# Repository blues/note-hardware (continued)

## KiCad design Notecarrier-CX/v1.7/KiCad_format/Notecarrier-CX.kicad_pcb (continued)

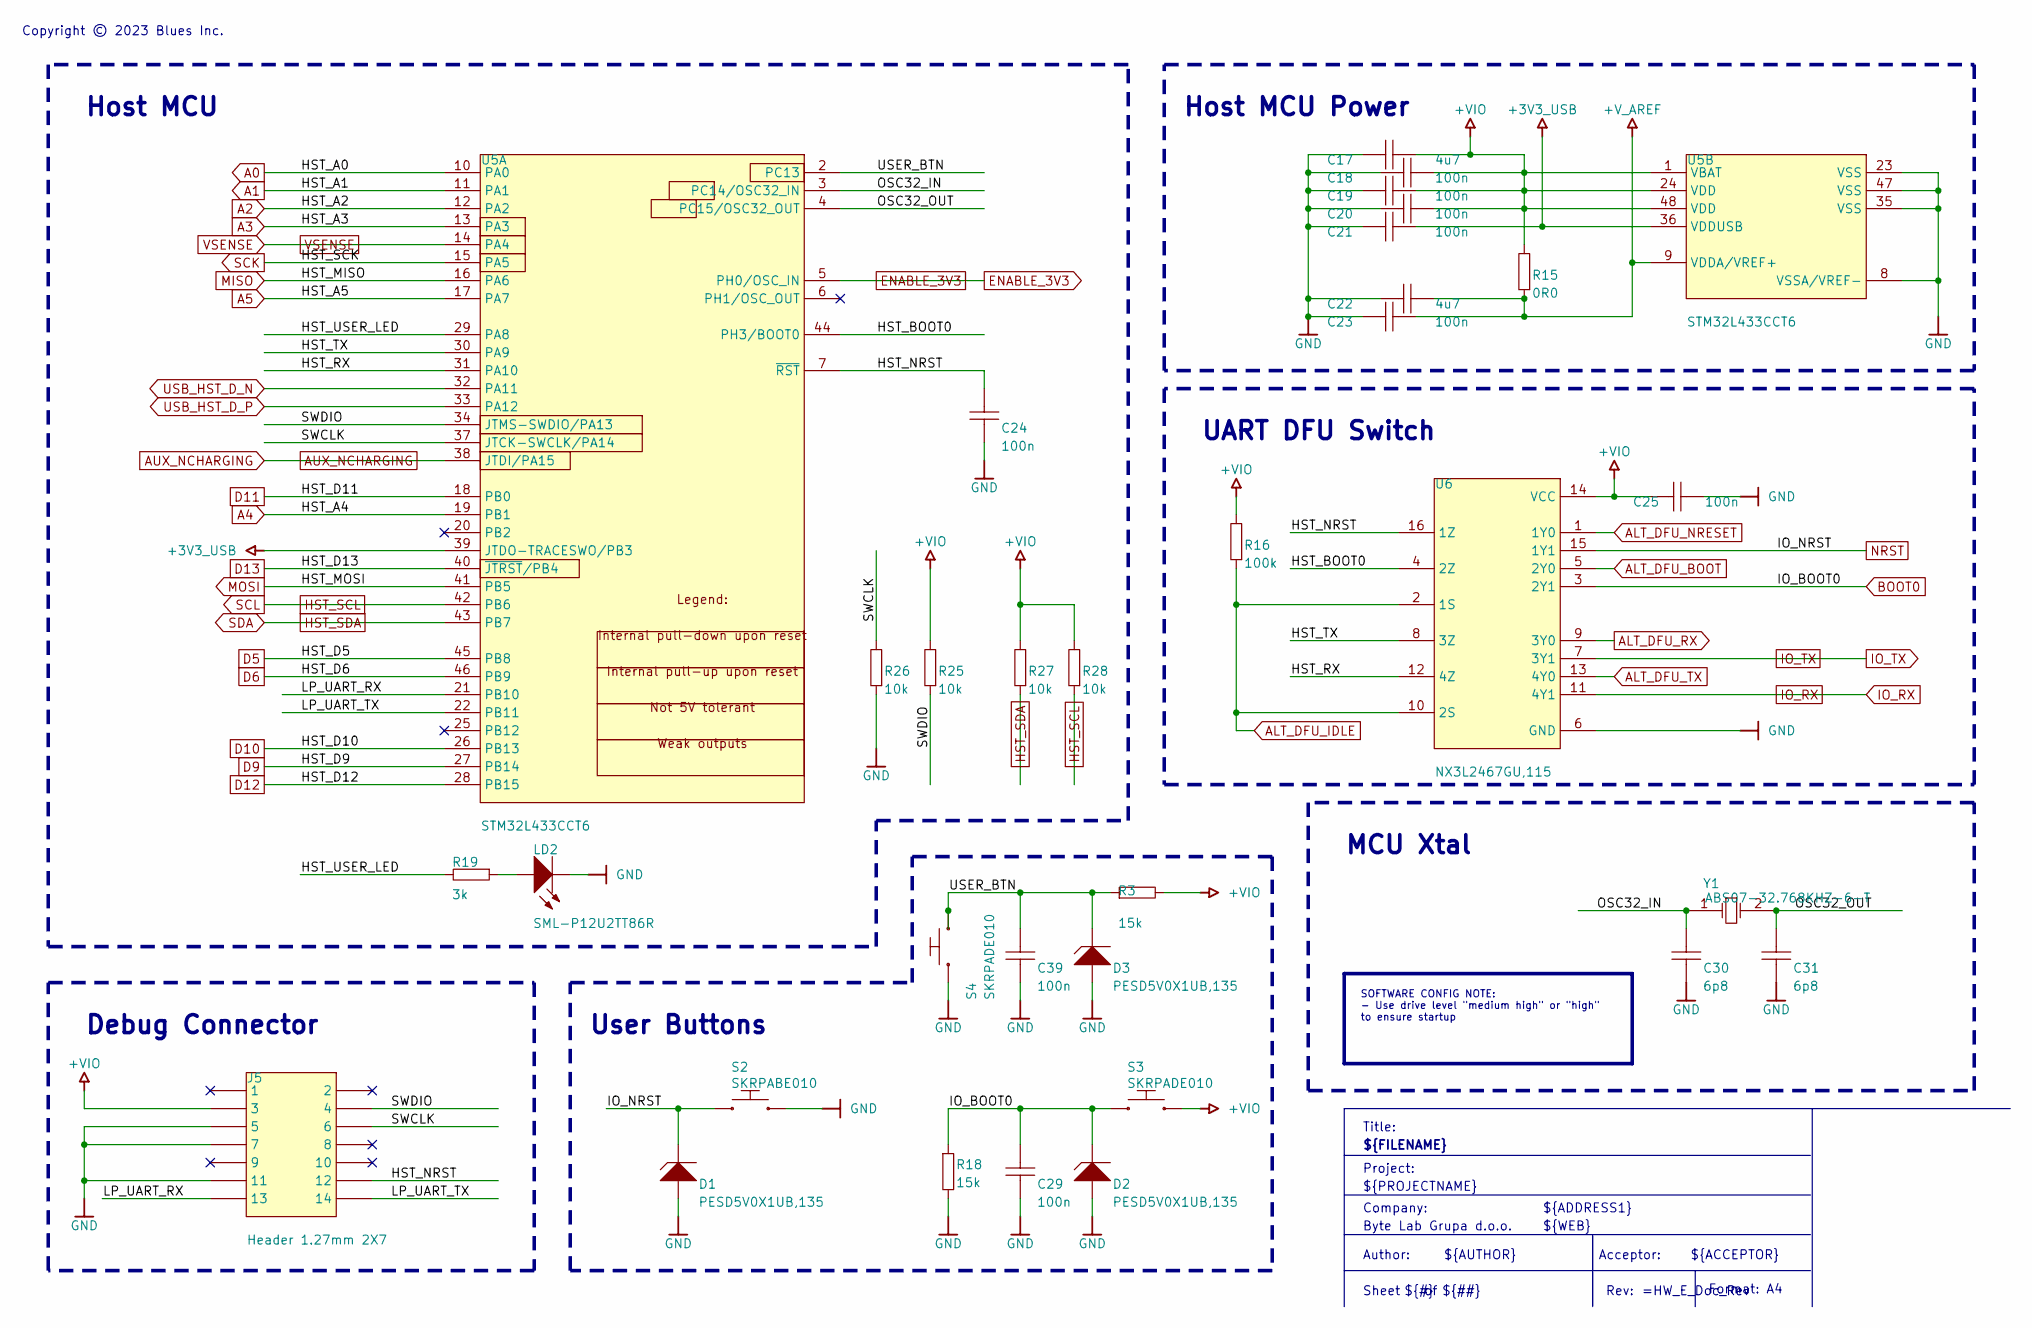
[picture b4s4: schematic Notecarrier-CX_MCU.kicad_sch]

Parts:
C17, C22: 4u7; C-0603; MANUFACTURER PART NUMBER N/A
C18, C19, C20, C21, C23, C24, C25, C29, C39: 100n; C-0402; MANUFACTURER PART NUMBER N/A
C30, C31: 6p8; C-0402; MANUFACTURER PART NUMBER CL05C6R8CB5NNNC
D1, D2, D3: PESD5V0X1UB,135; SOD-523F; MANUFACTURER PART NUMBER PESD5V0X1UB,135
J5: Header 1.27mm 2X7; Header 1.27mm 2X7 SMD; MANUFACTURER PART NUMBER FTSH-107-01-L-DV-K
LD2: SML-P12U2TT86R; LED-0402; MANUFACTURER PART NUMBER SML-P12U2TT86R
R3, R18: 15k; R-0402; MANUFACTURER PART NUMBER N/A
R15: 0R0; R-0603; MANUFACTURER PART NUMBER N/A
R16: 100k; R-0402; MANUFACTURER PART NUMBER N/A
R19: 3k; R-0402; MANUFACTURER PART NUMBER N/A
R25, R26, R27, R28: 10k; R-0402; MANUFACTURER PART NUMBER N/A
S2: SKRPABE010; Tact Switch SKRPADE010; MANUFACTURER PART NUMBER SKRPABE010
S3, S4: SKRPADE010; Tact Switch SKRPADE010; MANUFACTURER PART NUMBER SKRPADE010
U5: STM32L433CCT6; QFP50P900X900X160-48; MANUFACTURER PART NUMBER STM32L433CCT6
U6: NX3L2467GU,115; QFN40P180X260X55-16N; MANUFACTURER PART NUMBER NX3L2467GU,115
Y1: ABS07-32.768KHZ-6-T; XTAL_3.2x1.5 MM; MANUFACTURER PART NUMBER ABS07-32.768KHZ-6-T

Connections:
+3V3_USB: C21.2, U5.36 (VDDUSB), U5.39 (JTDO-TRACESWO/PB3); also elsewhere on the board
+VIO: C17.2, C18.2, C19.2, C20.2, C25.1, J5.3, R3.2, R15.2, R16.2, R25.2, R27.2, R28.2, S3.2, U5.1 (VBAT), U5.24 (VDD), U5.48 (VDD), U6.14 (VCC); also elsewhere on the board
+V_AREF: C22.2, C23.2, R15.1, U5.9 (VDDA/VREF+); also elsewhere on the board
/MCU/HST_BOOT0: U5.44 (PH3/BOOT0), U6.4 (2Z)
/MCU/HST_NRST: C24.2, J5.12, U5.7 (~RST), U6.16 (1Z)
/MCU/HST_RX: U5.31 (PA10), U6.12 (4Z)
/MCU/HST_TX: U5.30 (PA9), U6.8 (3Z)
/MCU/HST_USER_LED: R19.2, U5.29 (PA8)
/MCU/LP_UART_RX: J5.13, U5.21 (PB10)
/MCU/LP_UART_TX: J5.14, U5.22 (PB11)
/MCU/OSC32_IN: C30.2, U5.3 (PC14/OSC32_IN), Y1.1 (OSC1)
/MCU/OSC32_OUT: C31.2, U5.4 (PC15/OSC32_OUT), Y1.2 (OSC2)
/MCU/SWCLK: J5.6, R26.2, U5.37 (JTCK-SWCLK/PA14)
/MCU/SWDIO: J5.4, R25.1, U5.34 (JTMS-SWDIO/PA13)
/MCU/USER_BTN: C39.2, D3.2 (K), R3.1, S4.2, U5.2 (PC13)
A0: U5.10 (PA0); also elsewhere on the board
A1: U5.11 (PA1); also elsewhere on the board
A2: U5.12 (PA2); also elsewhere on the board
A3: U5.13 (PA3); also elsewhere on the board
A4: U5.19 (PB1); also elsewhere on the board
A5: U5.17 (PA7); also elsewhere on the board
ALT_DFU_BOOT: U6.5 (2Y0); also elsewhere on the board
ALT_DFU_IDLE: R16.1, U6.2 (1S), U6.10 (2S); also elsewhere on the board
ALT_DFU_NRESET: U6.1 (1Y0); also elsewhere on the board
ALT_DFU_RX: U6.9 (3Y0); also elsewhere on the board
ALT_DFU_TX: U6.13 (4Y0); also elsewhere on the board
AUX_NCHARGING: U5.38 (JTDI/PA15); also elsewhere on the board
BOOT0: C29.2, D2.2 (K), R18.1, S3.1, U6.3 (2Y1); also elsewhere on the board
D5: U5.45 (PB8); also elsewhere on the board
D6: U5.46 (PB9); also elsewhere on the board
D9: U5.27 (PB14); also elsewhere on the board
D10: U5.26 (PB13); also elsewhere on the board
D11: U5.18 (PB0); also elsewhere on the board
D12: U5.28 (PB15); also elsewhere on the board
D13: U5.40 (~JTRST/PB4); also elsewhere on the board
ENABLE_3V3: U5.5 (PH0/OSC_IN); also elsewhere on the board
GND: C17.1, C18.1, C19.1, C20.1, C21.1, C22.1, C23.1, C24.1, C25.2, C29.1, C30.1, C31.1, C39.1, D1.1 (A), D2.1 (A), D3.1 (A), J5.5, J5.7, J5.11, LD2.2 (K), R18.2, R26.1, S2.2, S4.1, U5.8 (VSSA/VREF-), U5.23 (VSS), U5.35 (VSS), U5.47 (VSS), U6.6 (GND); also elsewhere on the board
HST_SCL: R28.1, U5.42 (PB6); also elsewhere on the board
HST_SDA: R27.1, U5.43 (PB7); also elsewhere on the board
IO_RX: U6.11 (4Y1); also elsewhere on the board
IO_TX: U6.7 (3Y1); also elsewhere on the board
MISO: U5.16 (PA6); also elsewhere on the board
MOSI: U5.41 (PB5); also elsewhere on the board
NRST: D1.2 (K), S2.1, U6.15 (1Y1); also elsewhere on the board
unnamed: LD2.1 (A), R19.1
SCK: U5.15 (PA5); also elsewhere on the board
USB_HST_D_N: U5.32 (PA11); also elsewhere on the board
USB_HST_D_P: U5.33 (PA12); also elsewhere on the board
VSENSE: U5.14 (PA4); also elsewhere on the board

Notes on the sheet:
${COMPANY}
${#}
Debug Connector
UART DFU Switch
Host MCU Power
Copyright © 2023 Blues Inc.
Company:
${WEB}
${REVISION}
Author:
Format: A4
User Buttons
Project:
MCU Xtal
Rev:
${FILENAME}
${ADDRESS1}
Host MCU
${ACCEPTOR}
${##}
${AUTHOR}
Sheet
Acceptor:
Title:
${PROJECTNAME}
SOFTWARE CONFIG NOTE: - Use drive level "medium high" or "high" to ensure startup

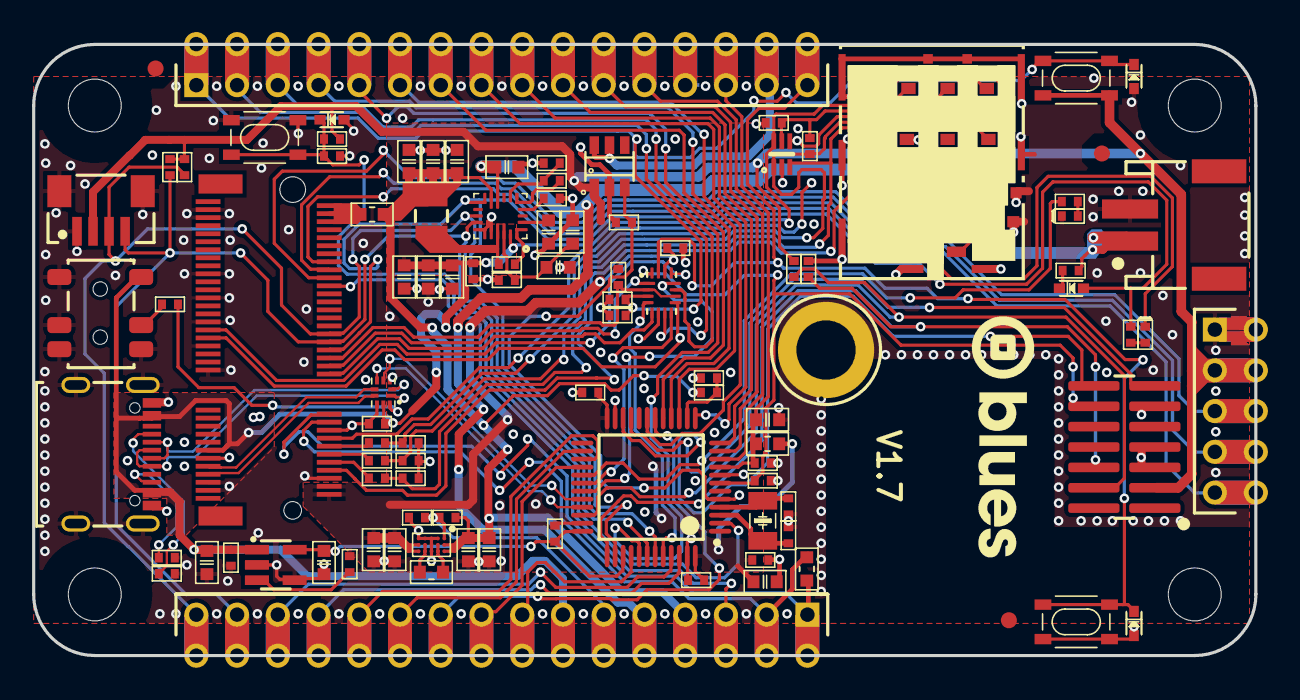
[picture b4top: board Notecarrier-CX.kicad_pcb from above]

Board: 4 copper layers, 76.2 x 38.1 mm, 101 parts (0 on the bottom side), 89 nets.

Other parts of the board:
FD1, FD2, FD5: Fiducial mark; Fiducial mark 1mm

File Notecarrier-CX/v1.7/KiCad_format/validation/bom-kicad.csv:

"Reference","Value","MPN","DNP"
"ASS1","KNOB M2.5x4-INOX","6000-168",""
"C1","10u","2006-831",""
"C2","100n","2000-908",""
"C3","33p","2001-377",""
"C4","33p","2001-377",""
"C5","33p","2001-377",""
"C6","10u","2006-831",""
"C7","10u","2006-831",""
"C8","47n/50V","2003-965",""
"C9","100n","2000-908",""
"C10","100n","2000-908",""
"C11","10u","2006-831",""
"C12","10u","2006-831",""
"C13","4u7","2003-721",""
"C14","10u","2006-831",""
"C15","100n","2004-296",""
"C16","4u7","2003-721",""
"C17","4u7","2003-721",""
"C18","100n","2000-908",""
"C19","100n","2000-908",""
"C20","100n","2000-908",""
"C21","100n","2000-908",""
"C22","4u7","2003-721",""
"C23","100n","2000-908",""
"C24","100n","2000-908",""
"C25","100n","2000-908",""
"C26","4u7","2003-721",""
"C27","100n","2000-908",""
"C28","4u7","2003-721",""
"C29","100n","2000-908",""
"C30","6p8","2001-291",""
"C31","6p8","2001-291",""
"C32","100n","2000-908",""
"C33","10u","2006-831",""
"C34","10u","2006-831",""
"C35","10u","2006-831",""
"C36","10u","2006-831",""
"C37","10u","2006-831",""
"C38","10u","2006-831",""
"C39","100n","2000-908",""
"D1","PESD5V0X1UB,135","2004-110",""
"D2","PESD5V0X1UB,135","2004-110",""
"D3","PESD5V0X1UB,135","2004-110",""
"D4","1N4148WT-7","2001-986",""
"J1","BM04B-SRSS-TB(LF)(SN)","2007-322",""
"J3","MDT580E01002","2009-243",""
"J4","SF72S006VBDR2500","2007-458",""
"J5","Header 1.27mm 2X7","2009-203",""
"L1","MCKK1608T1R0MN","2003-989",""
"L2","3u3","2004-215",""
"LD1","SML-P12WTT86R","2007-660",""
"LD2","SML-P12U2TT86R","2006-852",""
"P3","12402012E212A","2008-437",""
"P5","S2B-PH-SM4-K-TB","2007-662",""
"R1","5k1","2004-098",""
"R2","5k1","2004-098",""
"R3","15k","2001-157",""
"R4","0R0","2000-723","DNP"
"R5","22R","2001-170",""
"R6","22R","2001-170",""
"R7","15k","2001-157",""
"R8","22R","2001-170",""
"R9","0R0","2000-723",""
"R10","10M","2002-832",""
"R11","3k","2001-570",""
"R12","3k","2001-570",""
"R13","11k","2004-237",""
"R14","15k","2001-157",""
"R15","0R0","2000-723",""
"R16","100k","2000-727",""
"R17","1M","2000-734",""
"R18","15k","2001-157",""
"R19","3k","2001-570",""
"R20","11k","2004-237",""
"R21","1M","2000-734",""
"R22","11k","2004-237",""
"R23","10M","2002-832",""
"R24","4M3","2007-009",""
"R25","10k","2000-729",""
"R26","10k","2000-729",""
"R27","10k","2000-729",""
"R28","10k","2000-729",""
"S1","SSSS820101","2009-940",""
"S2","SKRPABE010","2009-324",""
"S3","SKRPADE010","2007-145",""
"S4","SKRPADE010","2007-145",""
"STANDOFF1","9774040151R","6000-267",""
"TVS1","PESD5V0L5UV,125","2007-452",""
"U1","NX3DV42GU","2005-299",""
"U2","RT6160BWSC","2008-326",""
"U3","BQ25628ERYKR","2008-206",""
"U4","TPS22917DBVR","2008-396",""
"U5","STM32L433CCT6","2009-272",""
"U6","NX3L2467GU,115","2009-148",""
"U7","TLV77033PDBVR","2009-790",""
"Y1","ABS07-32.768KHZ-6-T","2005-489",""

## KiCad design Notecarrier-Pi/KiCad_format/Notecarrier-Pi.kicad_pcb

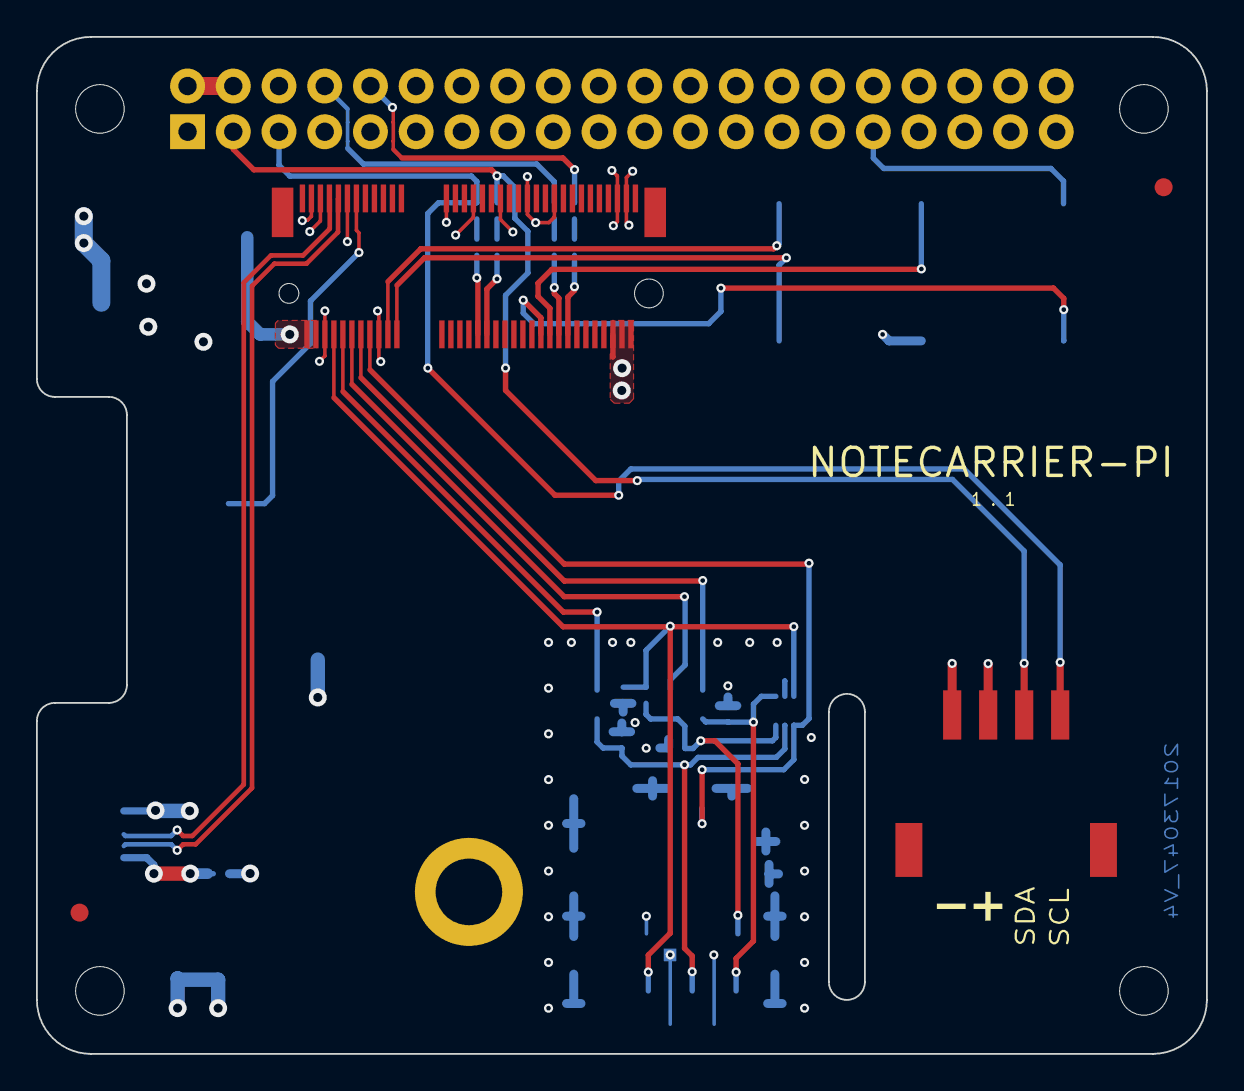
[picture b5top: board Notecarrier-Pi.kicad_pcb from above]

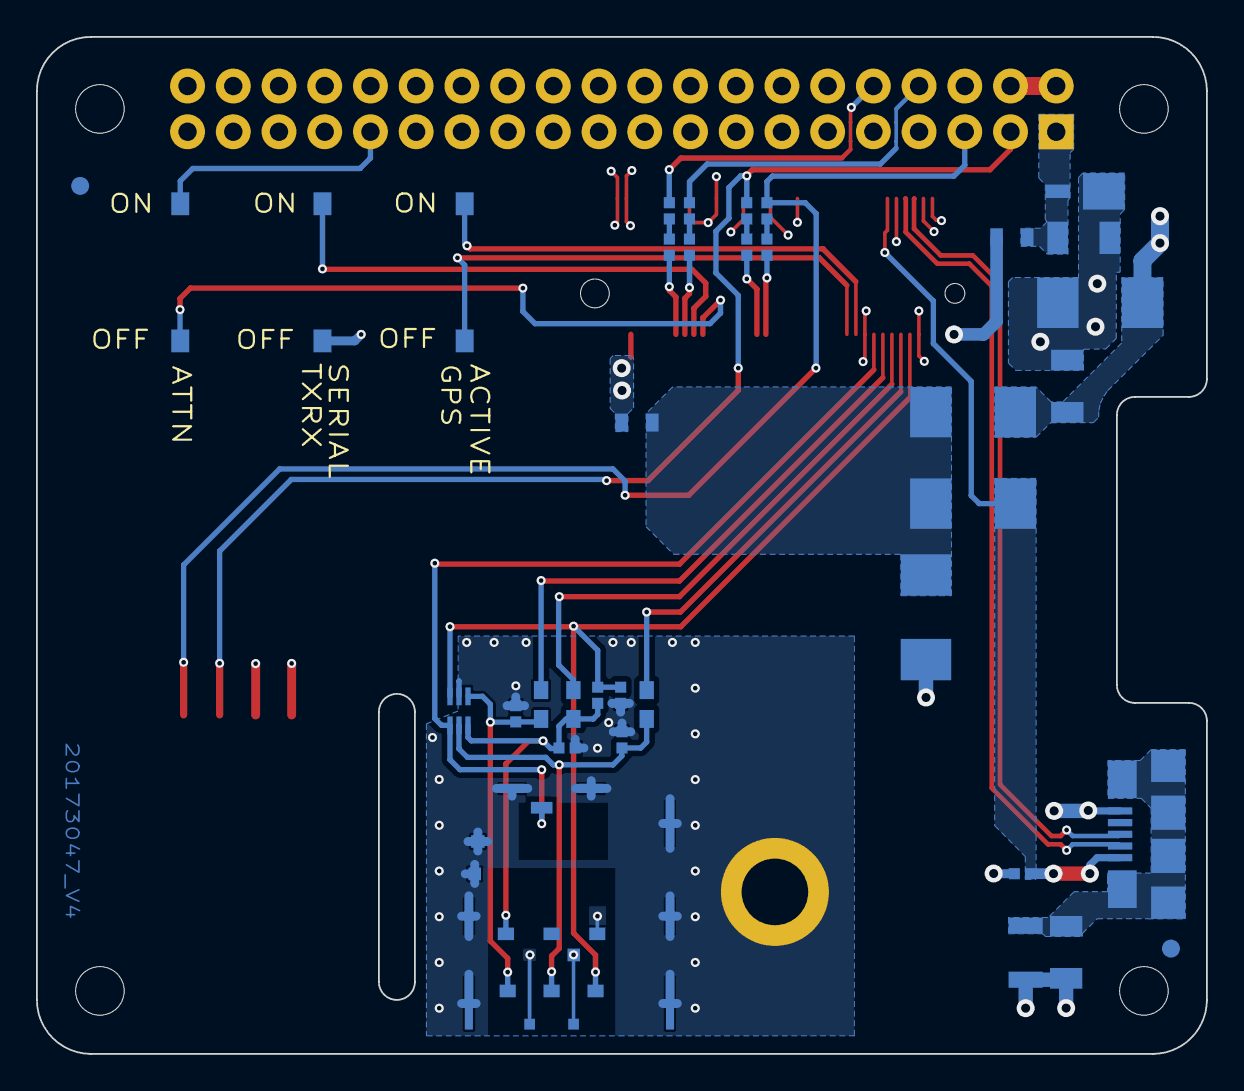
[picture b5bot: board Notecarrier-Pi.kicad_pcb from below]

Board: 4 copper layers, 65.0 x 56.5 mm, 46 parts (37 on the bottom side), 35 nets.

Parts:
C1, C2: 22u/25V-X5R; CS-C-1206
C3, C7: 100n/16V; CS-C-0402
C4, C5, C6: 33p/50V-C0G; CS-C-0402
C8: 10n/1kV; CS-C-1206
DS1, DS2: STPS3H100U; SMB
DSW1, DSW2, DSW3: DIP-SW-CHS-01TB; DSS-CHS-01TB
F1: SF-0603F150-2; FS-0603
F2: 3.5A/32V; FS-0603
FID1, FID2, FID3, FID4: TPS; FIDUCIAL
H1, H2, H3, H4: MountingHole; FORO-0270-U_smaller-clearance
J1: 2223; J-20x2-0254-FDT-SSQX03
J2: NanoSIM - SF72S006VBAR2500; J-NANOSIM-SF72S006VBA_NO-FILL
J3: MDT420E01001; J-75-0050-MOS-M2-E
J4: 10118192-0002LF; J-5-0065-FOS-USB10118192-NOF
J5: GROVE; J-4-0200-MOS-GROVE_NO-SILK
OBJ1: 9774025151R; DIST-WASMSIM0250
R1, R2, R3: 22R; RS-0603
R4: 15k; RS-0402
R5: 1M; RS-1206
R6, R7, R8, R9, R10, R11, R12, R13: 100R; RS-0402
TVS1, TVS3: SM6T6V8A; SMB
TVS2: SM2T3V3A; D-DO216AA_NO-SILK
TVS4: ESDLC5V0M5-TP; SOT666_NO-SILK

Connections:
/ATTN: DSW3.2, J1.31
/AUX_EN: DSW2.2, J3.56 (AUX_EN_P)
/AUX_RX: J1.8, R10.1
/AUX_RX_P: J3.58 (AUX_RX_P), R11.2
/AUX_TX: J1.10, R12.1
/AUX_TX_P: J3.60 (AUX_TX_P), R13.2
/SCL: J1.5, J5.1, R6.1
/SDA: J1.3, J5.2, R8.1
/SIM_CLK: J3.14 (SIM_CLK), R3.1
/SIM_IO: J3.12 (SIM_IO), R1.1
/SIM_NPRESENT: J2.DSW, J3.16 (SIM_NPRESENT), TVS4.4 (K3)
/SIM_RST: J3.10 (SIM_RST), R2.1
/SIM_VCC: C3.1, J2.C1 (VCC), J3.8 (SIM_VCC), R4.2, TVS4.3 (K2)
/USB_DM: J3.9 (USB_DM), J4.2 (D-)
/USB_DP: J3.7 (USB_DP), J4.3 (D+)
GND: C1.2, C2.2, C3.2, C4.2, C5.2, C6.2, C7.2, C8.2, J1.6, J1.9, J1.14, J1.20, J1.25, J1.30, J1.34, J1.39, J2.C5 (GND), J2.CSW, J2.SH, J3.3 (GND), J3.5 (GND), J3.6 (GND), J3.11 (GND), J3.18 (GND), J3.33 (GND), J3.39 (GND), J3.45 (GND), J3.51 (GND), J3.57 (GND), J3.71 (GND), J3.73 (GND), J4.5 (GND), J5.4, OBJ1.1, R5.2, TVS1.2 (A2), TVS2.2 (A2), TVS3.2 (A2), TVS4.2 (A)
unnamed: C5.1, J2.C3 (CLK), R3.2, TVS4.1 (K1)
unnamed: C6.1, J2.C7 (I/O), R1.2, R4.1, TVS4.6 (K5)
unnamed: C4.1, J2.C2 (RST), R2.2, TVS4.5 (K4)
unnamed: DSW3.1, J3.54 (ATTN_P)
unnamed: J3.40 (SCL_P), R7.2
unnamed: J3.42 (SDA_P), R9.2
unnamed: DSW1.1, J3.22 (VACT_GPS_IN)
unnamed: C8.1, J4.6 (Shield), R5.1
unnamed: R6.2, R7.1
unnamed: R8.2, R9.1
unnamed: R10.2, R11.1
unnamed: R12.2, R13.1
V+: C2.1, DS2.2 (A), J1.2, J1.4, TVS3.1 (A1)
VACT_GPS_OUT: DSW1.2, J3.20 (VACT_GPS_OUT)
VIO: C1.1, F1.1, J1.1, TVS2.1 (A1)
VIO_P: DSW2.1, F1.2, J3.2 (VIO_P), J3.4 (VIO_P), J5.3
VMODEM: DS1.1 (K), DS2.1 (K), F2.1, TVS1.1 (A1)
VMODEM_P: F2.2, J3.70 (VMODEM_P), J3.72 (VMODEM_P), J3.74 (VMODEM_P)
VUSB: C7.1, DS1.2 (A), J3.13 (VUSB), J4.1 (VBUS)

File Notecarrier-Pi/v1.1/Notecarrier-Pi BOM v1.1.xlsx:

PROJECT |  | 2017-3047 (NOTECARRIER-M2-PI) |  | Blues Inc
REVISION |  | 4
SCHEMATIC |  | 20173047_NOTECARRIER-M2-PI_V4
DATA |  | 23/09/2020
Item | Quantity | Reference | Part | MPN | Description | Temperature | Distributor | Type | Package | Database
1 | 1 | CS1 | CS V4 4L 18um |  | C.S. NOTECARRIER-M2-PI V4 (65X56.5)mm 4L/SO/SR ENIG TG150 sp=1.6mm Cu=18um | TG150 | WE
2 | 2 | C1,C2 | 22u/25V-X5R |  | CHIP CAP.CER. 22uF 25V 10% X5R 1206 | -55°..+85° | FAE | SMD | CS-C-1206 | 30650
3 | 2 | C3,C7 | 100n/16V |  | CHIP CAP.CER. 100nF 16V 10% X7R 0402 |  | FAE | SMD | CS-C-0402 | 22452
4 | 3 | C4,C5,C6 | 33p/50V-C0G |  | CHIP CAP.CER. 33pF 50V 5% C0G 0402 |  | FAE | SMD | CS-C-0402 | 38594
5 | 1 | C8 | 10n/1kV |  | CHIP CAP.CER. 10nF 1000V 10% X7R 1206 |  | FAE | SMD | CS-C-1206 | 28470
6 | 3 | DSW1,DSW2,DSW3 | DIP-SW-CHS-01TB |  | DIP SWITCH 1P/D NERO CHS-01TB COPAL SMT | -40°..+85° | FAE | SMD | DSS-CHS-01TB | 33083
7 | 2 | DS1,DS2 | STPS3H100U | STPS3H100U | DIODO SCHOTTKY 3A 100V STPS3H100U SMB SMT |  | FAE | SMD | SMB | 40665
8 | 1 | F1 | SF-0603F150-2 | SF-0603F150-2 | FUSIBILE RAPIDO 1.5A 32V 0603 SF-0603F150-2 BOURNS SMT | -40°..+105° | FAE | SMD | FS-0603 | 32505
9 | 1 | F2 | 3.5A/32V | 0603SFV350F/32-2 | FUSIBILE RAPIDO 3.5A 32V 0603 0603SFV350F/32-2 LITTELFUSE SMT | -55°..+125° | FAE | SMD | FS-0603 | 40054
10 | 1 | J1 | 2223 | 2223 | STRIP 20P F/D DOPPIA FILA P=2.54 2223 ADAFRUIT | -40..+105 | FAE | THT | J-20X2-0254-FDT-SSQx03 | STRIP 20P F/D DOPPIA FILA P=2.54 2223 ADAFRUIT
11 | 1 | J2 | NanoSIM - SF72S006VBAR2500 | SF72S006VBAR2500 | CONN. NANOSIM 8P F/90° PUSH-PUSH SF72S006VBAR2500 JAE ELECTRONICS SMT | -25°..+85° | FAE | SMD | J-NANOSIM-SF72S006VBA | 41049
12 | 1 | J3 | MDT420E01001 |  | CONN. M.2 75P M/90° P=0.5 MDT420E01001 AMPHENOL SMT | -40°..+80° | FAE | SMD | J-75-0050-MOS-M2-E | 44633
13 | 1 | J4 | 10118192-0002LF | 10118192-0002LF | CONN. USB F/90° TIPO MICRO-B C.S. 10118192-0002LF FCI SMT | -30°..+80° | FAE | SMD | J-5-0065-FOS-USB10118192-NOF | 47781
14 | 1 | J5 | GROVE |  | CONN. GROVE 4P M/90° P=2 1125R-SMT-4P SEEDSTUDIO SMT |  | FAE | SMD | J-4-0200-MOS-GROVE | 45891
15 | 1 | OBJ1 | 9774025151R |  | DISTANZ. CIL. METALLO 5.1X2.5 9774025151R W.E SMT |  | FAE | SMD | DIST-WASMSIM0250 | 44635
16 | 3 | R1,R2,R3 | 22R |  | CHIP RES. 22R 0603 1/16W 1% |  | FAE | SMD | RS-0603 | 20385
17 | 1 | R4 | 15k |  | CHIP RES. 15K 0402 1/16W 1% | -55°..+155° | FAE | SMD | RS-0402 | 40387
18 | 1 | R5 | 1M |  | CHIP RES. 1M 1206 1/4W 1% |  | FAE | SMD | RS-1206 | 28883
19 | 8 | R6,R7,R8,R9,R10,R11,R12,R13 | 100R |  | CHIP RES. 100R 0402 1/16W 1% |  | FAE | SMD | RS-0402 | 26315
20 | 2 | TVS1,TVS3 | SM6T6V8A |  | DIODO TVS TRANSIL UNIDIR. 600W 6.8V SM6T6V8A SMB SMT |  | FAE | SMD | SMB | 14165
21 | 1 | TVS2 | SM2T3V3A |  | DIODO TVS TRANSIL UNDIR. 200W 3.6V SM2T3V3A DO216AA SMT |  | FAE | SMD | D-DO216AA | 38895
22 | 1 | TVS4 | ESDLC5V0M5-TP |  | DIODO TVS TRANSIL UNIDIR. 20W 5V ESDLC5V0M5-TP SOT563 SMT | -65°..+150° | FAE | SMD | SOT666 | 44643
 | 39 |  |  |  |  |  | 1
MECHANICAL
1 | 1 | ASS1 | KNOB M2.5x4 - INOX |  | VITE TCEI 2.5X4 ESAGONO INCASSATO A2 INOX |  | FAE | THT |  | 48266
 | 1 |  |  |  |  |  | 0
NOT MOUNTED
1 | 4 | FID1,FID2,FID3,FID4 | TPS |  | FIDUCIAL |  | FAE | SMD | FIDUCIAL
